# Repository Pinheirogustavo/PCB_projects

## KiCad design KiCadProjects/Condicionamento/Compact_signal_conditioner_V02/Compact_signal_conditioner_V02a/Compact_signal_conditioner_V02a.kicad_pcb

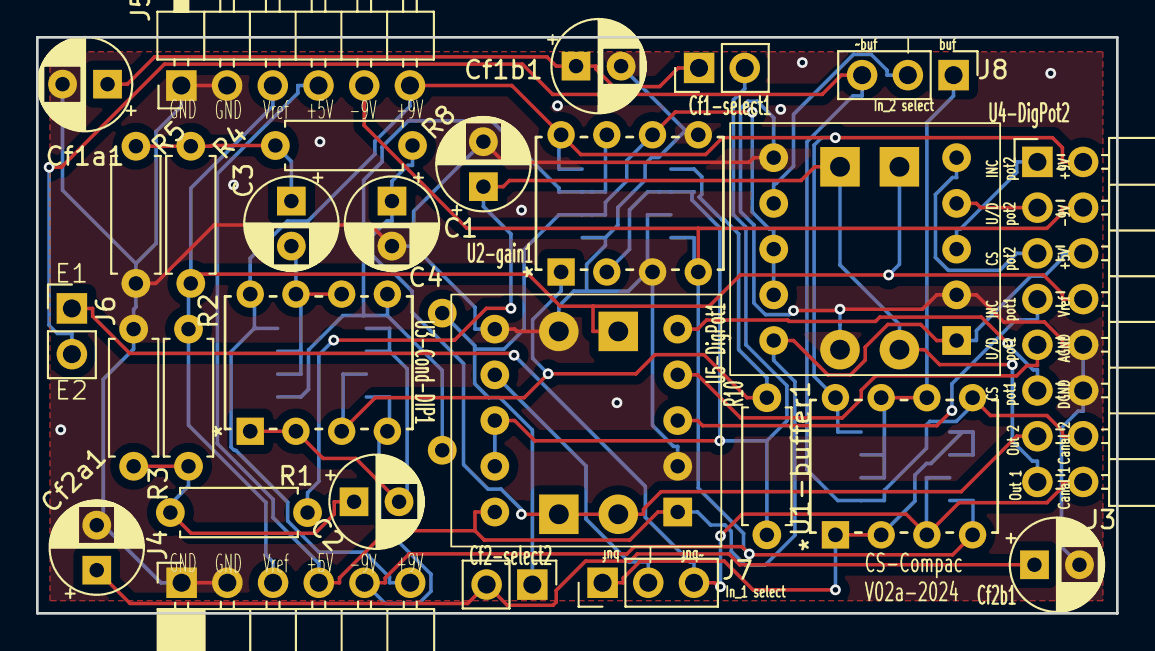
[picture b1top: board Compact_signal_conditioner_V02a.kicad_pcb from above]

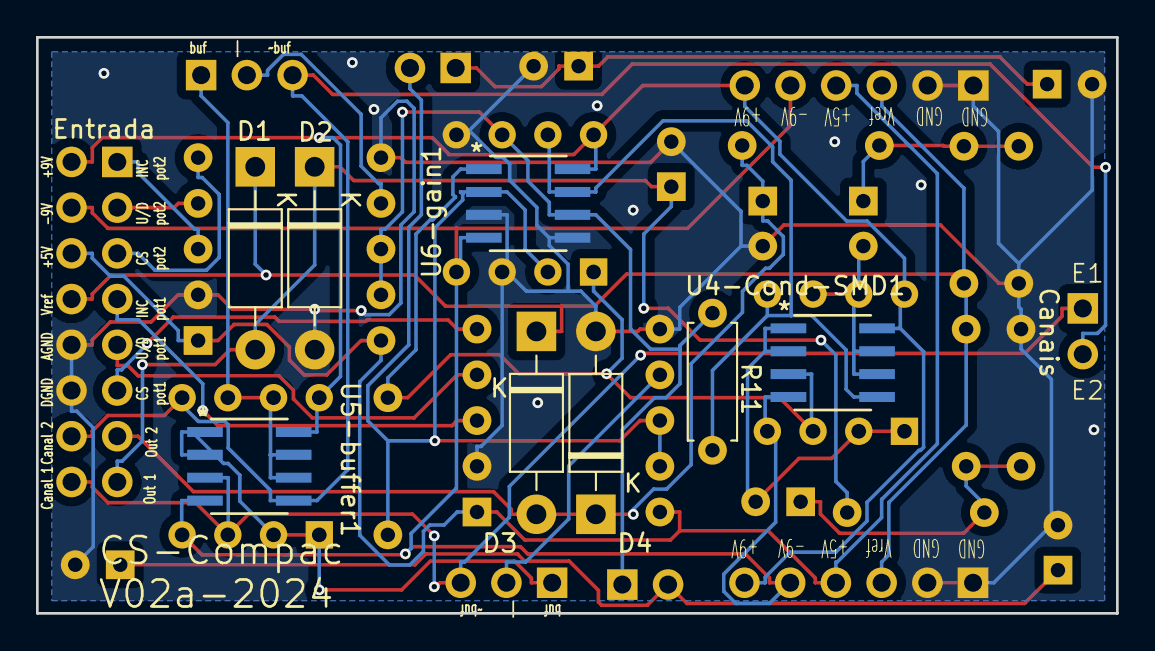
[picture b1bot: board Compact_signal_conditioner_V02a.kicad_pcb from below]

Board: 2 copper layers, 60.0 x 32.0 mm, 36 parts (8 on the bottom side), 29 nets.

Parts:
C1, C4: 470 pF; CP_Radial_D5.0mm_P2.50mm
C2, C3: 1 uF; CP_Radial_D5.0mm_P2.50mm
Cf1-select1: jumper cf1; PinHeader_1x02_P2.54mm_Vertical
Cf1a1, Cf1b1, Cf2a1, Cf2b1: C; CP_Radial_D5.0mm_P2.50mm
Cf2-select2: jumper cf2; PinHeader_1x02_P2.54mm_Vertical
D1, D2, D3, D4: 1N5819; D_DO-41_SOD81_P10.16mm_Horizontal
J3: Entrada; PinHeader_2x08_P2.54mm_Horizontal
J4: in; PinSocket_1x06_P2.54mm_Horizontal
J5: out; PinHeader_1x06_P2.54mm_Horizontal
J6: Canais; PinHeader_1x02_P2.54mm_Vertical
J7: In_1 select; PinHeader_1x03_P2.54mm_Vertical
J8: In_2 select; PinHeader_1x03_P2.54mm_Vertical
R1, R8: 220; R_Axial_DIN0207_L6.3mm_D2.5mm_P7.62mm_Horizontal
R2, R3, R4, R5: 100k; R_Axial_DIN0207_L6.3mm_D2.5mm_P7.62mm_Horizontal
R10, R11: 51k; R_Axial_DIN0207_L6.3mm_D2.5mm_P7.62mm_Horizontal
U1-buffer1, U2-gain1, U3-Cond-DIP1: AD828AN; N_8_ADI
U4-Cond-SMD1, U5-buffer1, U6-gain1: AD8056ARZ; R_8_ADI
U4-DigPot2, U5-DigPot1: X9c10x; X9c10X_module

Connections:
+5V: J3.3, J4.4, J5.4, U4-DigPot2.1 (VCC), U4-DigPot2.10 (VCC), U5-DigPot1.1 (VCC), U5-DigPot1.10 (VCC)
+9V: J3.1, J4.6, J5.6, U1-buffer1.8 (V+), U2-gain1.8 (V+), U3-Cond-DIP1.8 (V+), U4-Cond-SMD1.8 (VS+), U5-buffer1.8 (VS+), U6-gain1.8 (VS+)
-9V: J3.2, J4.5, J5.5, U1-buffer1.4 (V-), U2-gain1.4 (V-), U3-Cond-DIP1.4 (V-), U4-Cond-SMD1.4 (VS-), U5-buffer1.4 (VS-), U6-gain1.4 (VS-)
Canal_1: J3.8, J6.1, J7.3, U1-buffer1.3 (+IN1), U5-buffer1.3 (IN1+)
Canal_1_buffer: J7.1, U1-buffer1.1 (OUT1), U1-buffer1.2 (-IN1), U5-buffer1.1 (OUT1), U5-buffer1.2 (IN1-)
Canal_1_gain: R10.2, U2-gain1.1 (OUT1), U3-Cond-DIP1.3 (+IN1), U4-Cond-SMD1.3 (IN1+), U6-gain1.1 (OUT1)
Canal_2: J3.7, J6.2, J8.3, U1-buffer1.5 (+IN2), U5-buffer1.5 (IN2+)
Canal_2_buffer: J8.1, U1-buffer1.6 (-IN2), U1-buffer1.7 (OUT2), U5-buffer1.6 (IN2-), U5-buffer1.7 (OUT)
Canal_2_gain: R11.2, U2-gain1.7 (OUT2), U3-Cond-DIP1.5 (+IN2), U4-Cond-SMD1.5 (IN2+), U6-gain1.7 (OUT)
Earth: C1.2, C4.2, Cf1a1.2, Cf1b1.2, Cf2a1.2, Cf2b1.2, D2.2 (A), D4.2 (A), J3.5, J3.6, J4.1, J4.2, J5.1, J5.2, R3.2, R5.2, U2-gain1.3 (+IN1), U2-gain1.5 (+IN2), U4-DigPot2.2 (GND), U4-DigPot2.6 (GND), U5-DigPot1.2 (GND), U5-DigPot1.6 (GND), U6-gain1.3 (IN1+), U6-gain1.5 (IN2+)
In_gain_1: J7.2, U5-DigPot1.7 (RL)
In_gain_2: J8.2, U4-DigPot2.7 (RL)
unnamed: Cf1-select1.1, Cf1a1.1, Cf1b1.1
unnamed: Cf2-select2.2, Cf2a1.1, Cf2b1.1
Out_1: C1.1, D1.2 (A), D2.1 (K), J3.10, R1.2
Out_2: C4.1, D3.2 (A), D4.1 (K), J3.9, R8.2
Pot1_CS_(X9c104): J3.11, U5-DigPot1.5 (CS)
Pot1_X9c10x_INC: J3.13, U5-DigPot1.3 (INC)
Pot1_X9c10x_U/D: J3.12, U5-DigPot1.4 (U/D)
Pot2_CS_(X9c104): J3.14, U4-DigPot2.5 (CS)
Pot2_X9c10x_INC: J3.16, U4-DigPot2.3 (INC)
Pot2_X9c10x_U/D: J3.15, U4-DigPot2.4 (U/D)
Vref: D1.1 (K), D3.1 (K), J3.4, J4.3, J5.3, R2.1, R4.1
auxiliar_1: Cf1-select1.2, R10.1, U2-gain1.2 (-IN1), U5-DigPot1.8 (RW), U5-DigPot1.9 (RH), U6-gain1.2 (IN1-)
auxiliar_2: Cf2-select2.1, R11.1, U2-gain1.6 (-IN2), U4-DigPot2.8 (RW), U4-DigPot2.9 (RH), U6-gain1.6 (IN2-)
nó1: C2.2, U3-Cond-DIP1.1 (OUT1), U3-Cond-DIP1.2 (-IN1), U4-Cond-SMD1.1 (OUT1), U4-Cond-SMD1.2 (IN1-)
nó2: C2.1, R1.1, R2.2, R3.1
nó3: C3.2, U3-Cond-DIP1.6 (-IN2), U3-Cond-DIP1.7 (OUT2), U4-Cond-SMD1.6 (IN2-), U4-Cond-SMD1.7 (OUT)
nó4: C3.1, R4.2, R5.1, R8.1

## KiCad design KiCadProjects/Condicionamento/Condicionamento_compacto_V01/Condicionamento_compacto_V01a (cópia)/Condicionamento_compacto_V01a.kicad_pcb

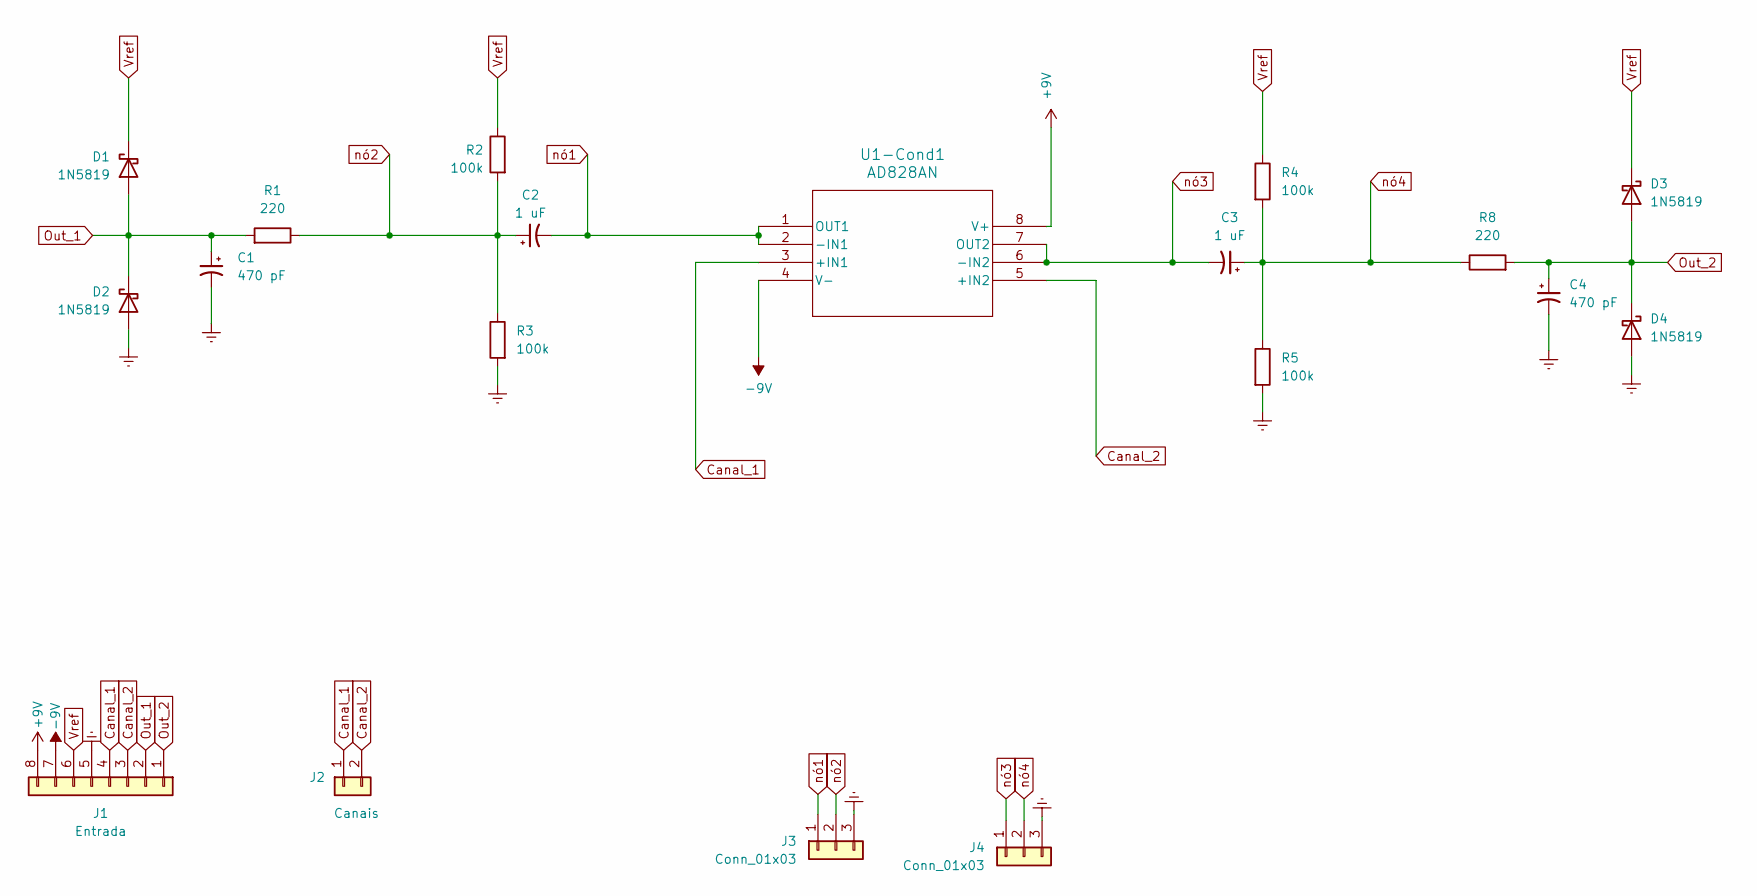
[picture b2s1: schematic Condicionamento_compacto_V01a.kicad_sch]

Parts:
C1, C4: 470 pF; CP_Radial_D5.0mm_P2.50mm
C2, C3: 1 uF; CP_Radial_D5.0mm_P2.50mm
D1, D2, D3, D4: 1N5819; D_DO-41_SOD81_P10.16mm_Horizontal
J1: Entrada; PinSocket_1x08_P2.54mm_Vertical
J2: Canais; PinHeader_1x02_P2.54mm_Vertical
J3, J4: Conn_01x03; PinHeader_1x03_P2.54mm_Vertical
R1, R8: 220; R_Axial_DIN0207_L6.3mm_D2.5mm_P7.62mm_Horizontal
R2, R3, R4, R5: 100k; R_Axial_DIN0207_L6.3mm_D2.5mm_P7.62mm_Horizontal
U1-Cond1: AD828AN; N_8_ADI

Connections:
+9V: J1.8, U1-Cond1.8 (V+)
-9V: J1.7, U1-Cond1.4 (V-)
Canal_1: J1.4, J2.1, U1-Cond1.3 (+IN1)
Canal_2: J1.3, J2.2, U1-Cond1.5 (+IN2)
Earth: C1.2, C4.2, D2.2 (A), D4.2 (A), J1.5, J3.3, J4.3, R3.2, R5.2
Out_1: C1.1, D1.2 (A), D2.1 (K), J1.2, R1.2
Out_2: C4.1, D3.2 (A), D4.1 (K), J1.1, R8.2
Vref: D1.1 (K), D3.1 (K), J1.6, R2.1, R4.1
nó1: C2.2, J3.1, U1-Cond1.1 (OUT1), U1-Cond1.2 (-IN1)
nó2: C2.1, J3.2, R1.1, R2.2, R3.1
nó3: C3.2, J4.1, U1-Cond1.6 (-IN2), U1-Cond1.7 (OUT2)
nó4: C3.1, J4.2, R4.2, R5.1, R8.1

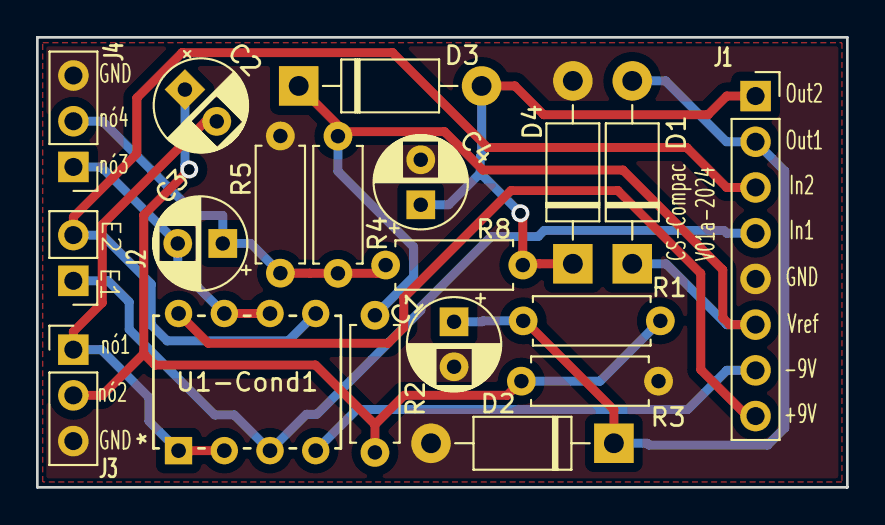
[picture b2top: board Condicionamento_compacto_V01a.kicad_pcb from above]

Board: 2 copper layers, 45.0 x 25.0 mm, 19 parts (0 on the bottom side), 12 nets.

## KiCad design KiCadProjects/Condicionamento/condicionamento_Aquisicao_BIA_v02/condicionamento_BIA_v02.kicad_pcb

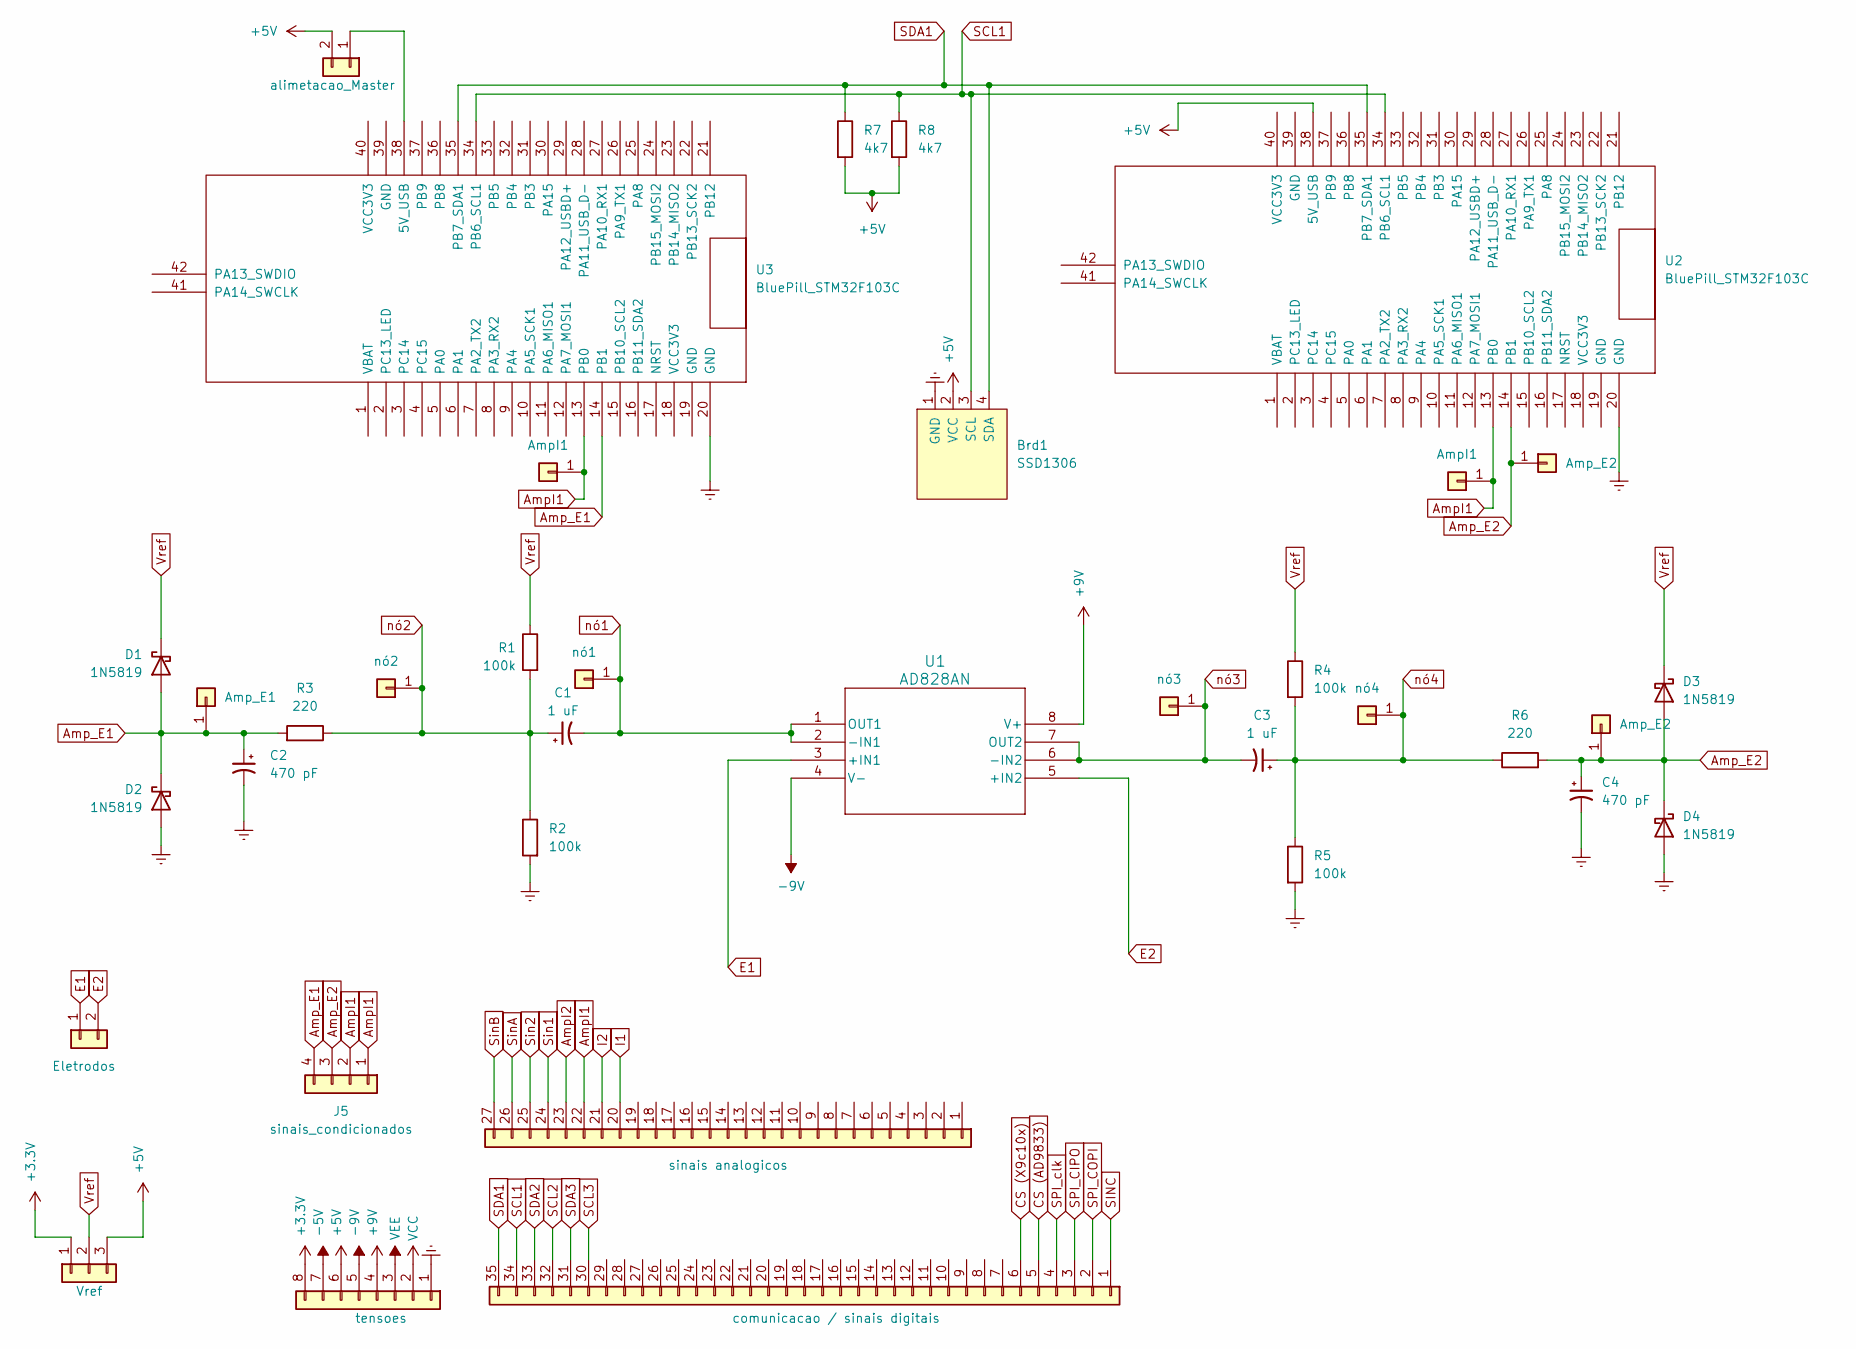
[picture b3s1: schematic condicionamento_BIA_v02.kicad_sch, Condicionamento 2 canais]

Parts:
Brd1: SSD1306; 128x64OLED
C1, C3: 1 uF; CP_Radial_D5.0mm_P2.50mm
C2, C4: 470 pF; CP_Radial_D5.0mm_P2.50mm
D1, D2, D3, D4: 1N5819; D_DO-41_SOD81_P10.16mm_Horizontal
J1: Vref; PinHeader_1x03_P2.54mm_Vertical
J2: tensoes; PinHeader_1x08_P2.54mm_Vertical
J3: sinais analogicos; PinHeader_1x27_P2.54mm_Vertical
J4: comunicacao / sinais digitais; PinHeader_1x35_P2.54mm_Vertical
J5: sinais_condicionados; PinHeader_1x04_P2.54mm_Horizontal
J6: alimetacao_Master; PinHeader_1x02_P2.54mm_Vertical
J7: Eletrodos; PinHeader_1x02_P2.54mm_Horizontal
J8: nó2; PinHeader_1x01_P2.54mm_Vertical
J9: nó1; PinHeader_1x01_P2.54mm_Vertical
J10: nó3; PinHeader_1x01_P2.54mm_Vertical
J11: nó4; PinHeader_1x01_P2.54mm_Vertical
J12: Amp_E1; PinHeader_1x01_P2.54mm_Vertical
J13, J16: Amp_E2; PinHeader_1x01_P2.54mm_Vertical
J15, J17: AmpI1; PinHeader_1x01_P2.54mm_Vertical
R1, R2, R4, R5: 100k; R_Axial_DIN0207_L6.3mm_D2.5mm_P7.62mm_Horizontal
R3, R6: 220; R_Axial_DIN0207_L6.3mm_D2.5mm_P7.62mm_Horizontal
R7, R8: 4k7; R_Axial_DIN0207_L6.3mm_D2.5mm_P7.62mm_Horizontal
U1: AD828AN; N_8_ADI
U2, U3: BluePill_STM32F103C

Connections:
+3.3V: J1.1, J2.8; also elsewhere on the board
+5V: Brd1.2 (VCC), J1.3, J2.6, J6.2, R7.2, R8.2, U2.38 (5V_USB); also elsewhere on the board
+9V: J2.4, U1.8 (V+)
-5V: J2.7
-9V: J2.5, U1.4 (V-)
AmpI1: J3.22, J5.1, J5.2, J15.1, J17.1, U2.13 (PB0), U3.13 (PB0)
AmpI2: J3.23
Amp_E1: C2.1, D1.2 (A), D2.1 (K), J5.4, J12.1, R3.2, U3.14 (PB1)
Amp_E2: C4.1, D3.2 (A), D4.1 (K), J5.3, J13.1, J16.1, R6.2, U2.14 (PB1)
CS (AD9833): J4.5
CS (X9c10x): J4.6
E1: J7.1, U1.3 (+IN1)
E2: J7.2, U1.5 (+IN2)
Earth: Brd1.1 (GND), C2.2, C4.2, D2.2 (A), D4.2 (A), J2.1, R2.2, R5.2, U2.20 (GND), U3.20 (GND); also elsewhere on the board
I1: J3.20
I2: J3.21
unnamed: J6.1, U3.38 (5V_USB)
SCL1: Brd1.3 (SCL), J4.34, R8.1, U2.34 (PB6_SCL1), U3.34 (PB6_SCL1); also elsewhere on the board
SCL2: J4.32
SCL3: J4.30
SDA1: Brd1.4 (SDA), J4.35, R7.1, U2.35 (PB7_SDA1), U3.35 (PB7_SDA1); also elsewhere on the board
SDA2: J4.33
SDA3: J4.31
SINC: J4.1
SPI_CIPO: J4.3
SPI_COPI: J4.2
SPI_clk: J4.4
Sin1: J3.24
Sin2: J3.25
SinA: J3.26
SinB: J3.27
VCC: J2.2
VEE: J2.3
Vref: D1.1 (K), D3.1 (K), J1.2, R1.1, R4.1; also elsewhere on the board
nó1: C1.2, J9.1, U1.1 (OUT1), U1.2 (-IN1)
nó2: C1.1, J8.1, R1.2, R2.1, R3.1
nó3: C3.2, J10.1, U1.6 (-IN2), U1.7 (OUT2)
nó4: C3.1, J11.1, R4.2, R5.1, R6.1

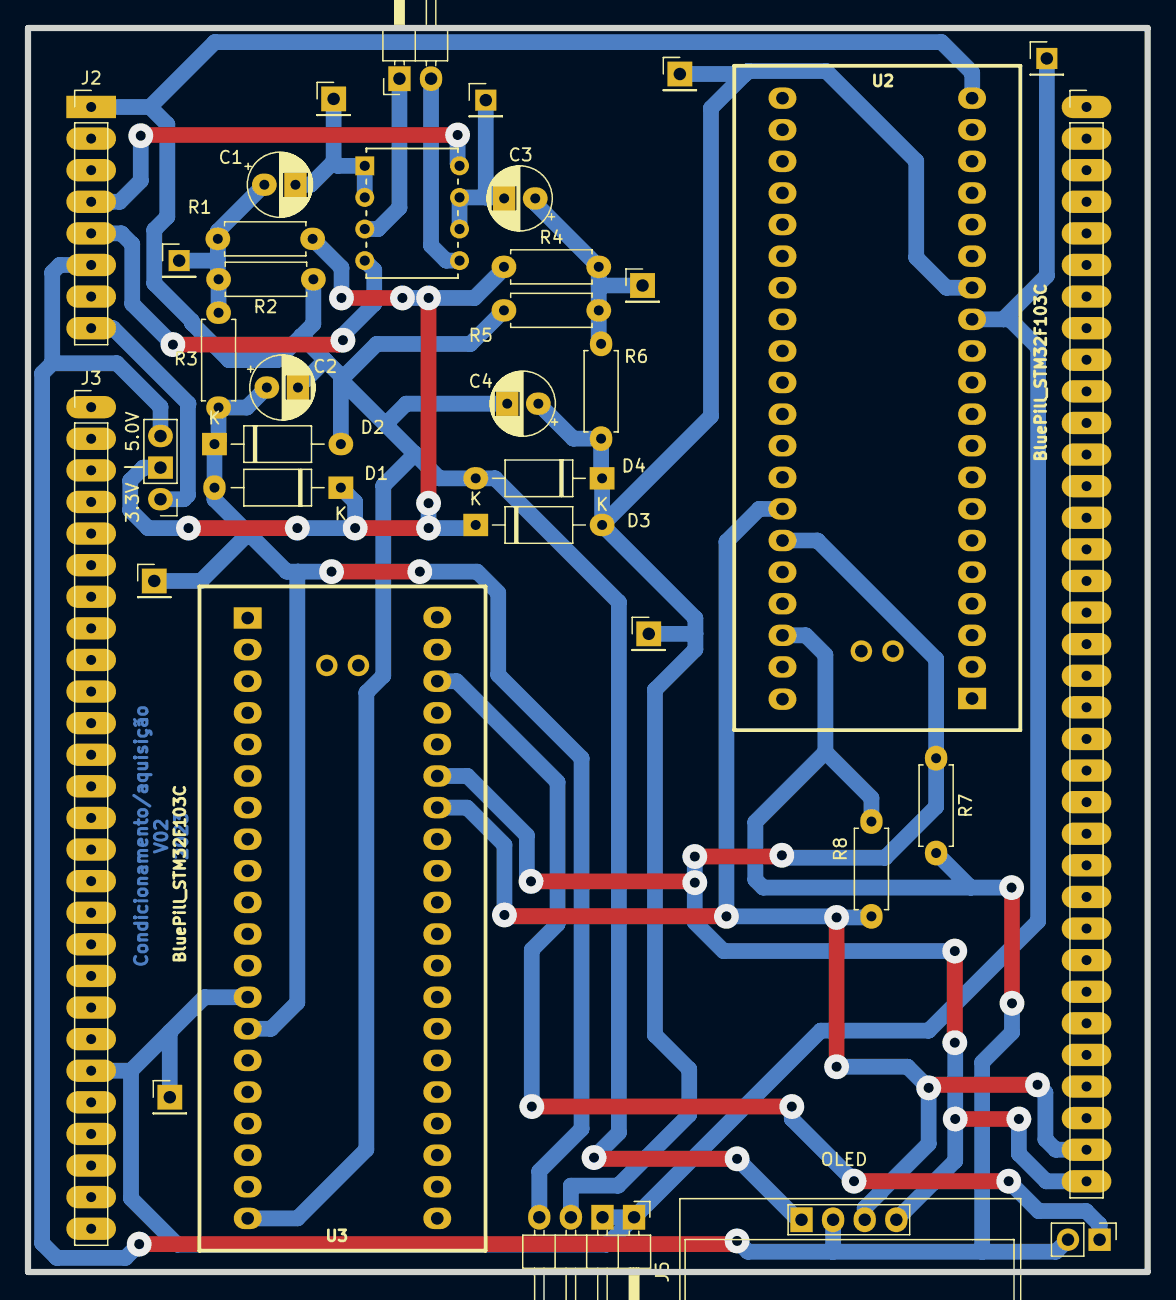
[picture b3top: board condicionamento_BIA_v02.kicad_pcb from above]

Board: 2 copper layers, 90.0 x 100.0 mm, 36 parts (0 on the bottom side), 18 nets.

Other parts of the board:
3.3V | 5.0V: Vref; PinHeader_1x03_P2.54mm_Vertical
OLED: SSD1306; 128x64OLED

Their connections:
+3.3V: 3.3V | 5.0V.1; also elsewhere on the board
+5V: 3.3V | 5.0V.3, OLED.2 (VCC); also elsewhere on the board
Earth: OLED.1 (GND); also elsewhere on the board
SCL1: OLED.3 (SCL); also elsewhere on the board
SDA1: OLED.4 (SDA); also elsewhere on the board
Vref: 3.3V | 5.0V.2; also elsewhere on the board

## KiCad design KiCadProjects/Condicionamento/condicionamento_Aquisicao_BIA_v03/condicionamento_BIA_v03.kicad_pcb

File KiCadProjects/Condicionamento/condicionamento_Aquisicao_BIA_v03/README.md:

# Circuito de condicionamento e aquisição de sinal

## Descrição Geral do projeto

Sistema projetado para permitir a aquisição de sinais por meio dos dois ADCs presentes em cada microcontrolador STM32.

Estágios: Sinais a serem condicionados &rarr; buffer &rarr; offset (valor médio do limite de entrada do ADC) &rarr; diodos de proteção ( limites de entrada do ADC) &rarr; Filtro anti-aliasing &rarr; sinal condicionado &rarr; ADC@STM32

## Sinais do circuito:

- AmplI1: Tensão de saída **já condicionada** do INA que monitora a corrente I1
- Amp_E1: Tensão medida pelo eletrodo proximal do pé/mão
- Amp_E2: Tensão medida pelo eletrodo proximal do pé/mão

##Cuidados a serem tomados

O conjunto de pinos **Vref** permite selecionar sinais e 3.3V e 5.0V. A escolha do sinal deve ser adequada ao limite de entrada dos pinos ADCs do microcontrolador utilizado. Para o STM32 esse limite é de 3.3V.

Todos os sinais que são enviados aos pinos de ADCs dos microcontroladores devem estar devidamente condicionados.

Sobre a alimentação dos microcontroladores: O par de pinos "alimentacao_Master" fornece uma alimentação de +5V  ao Master quando é fechado. Esse  par de pinos deve permanecer aberto quando o microcontrolador Master estiver conectado ao computador por meio de cabo USB, pois o pino de 5V do STM32 é diretamente conectada à alimentação fornecida por USB, sem qualquer circuito de proteção. O microcontrolador Slave está sempre conectado à alimentação de 5V do sistema. Somente conecte esse dispositivo ao computador se o sistema estiver desligado. 

## Estágios do circuito

#### Circuito de condicionamento

O circuito de condicionamento permite a adequada aquisição de sinal por meio de microcontrolador, garantindo que os sinais aplicados nas entradas do dispositivo não ultrapassem os limites de tensão e corrente suportados, além da adequada amostragem do sinal, por meio de filtro anti-aliasing. Esse circuito emprega o amplificador operacional dual AD826/828, o que permite o condicionamento de dois canais. Os estágios do circuito são: 

- buffer: amplificador operacional no modo seguidor, configuração de alta impedância de entrada que permite o adequado acoplamento entre os estágios do sistema, minimizando a interação entre eles.

- Offset: estágio que realiza um deslocamento (offset) do sinal de entrada, adequando os sinais alternados de correntes do circuito aos ADCs do microcontrolador, adicionando um sinal DC equivalente ao valor médio do limite de entrada dos ADCS. O valor de Vref deve ser definido pelo operador de acordo com esse limite.

- Diodos de proteção: não permitem que o sinal de entrada ultrapasse  os limites de entrada do conversor ADC. O valor de Vref deve ser definido pelo operador de acordo com esse limite.

- filtro anti-alising: Frequência de corte $F_c$:

$$F_c = \frac{1}{2\cdot\pi\cdot R\cdot C} = \frac{1}{2\cdot\pi\cdot220\cdot470\cdot10 ^{-12}} = 1,5 MHz$$

#### Microcontroladores

Dois microcontroladores são empregados nesse sistema de BIA, permitindo a leitura de 4 canais de medição. A comunicação entre eles é feita por meio do protocolo I2C. Ambos leem o sinal de amplitude da corrente medida pelo INA (AmpI1) em seus ADCs.

- STM32 Master

O par de pinos "alimentacao_Master" fornece uma alimentação de +5V quando é fechado. Esse  par de pinos deve permanecer aberto quando o microcontrolador estiver conectado ao computador por meio de cabo USB, pois o pino de 5V do STM32 é diretamente conectada à alimentação fornecida por USB, sem qualquer circuito de proteção.

> ADC1: Pino B0 recebe o sinal de amplitude de corrente AmpI1

> ADC2: Pino B1 recebe o sinal de amplitude de tensão do eletrodo de medição E1.

- STM32 Slave

O microcontrolador está sempre conectado à alimentação de 5V do sistema. Somente conecte esse dispositivo ao computador se o sistema estiver desligado. 

> ADC1: Pino B0 recebe o sinal de amplitude de corrente AmpI1

> ADC2: Pino B1 recebe o sinal de amplitude de tensão do eletrodo de medição E2.

## Esquemático

## PCB

## PCB-3D

## PCB Máscara

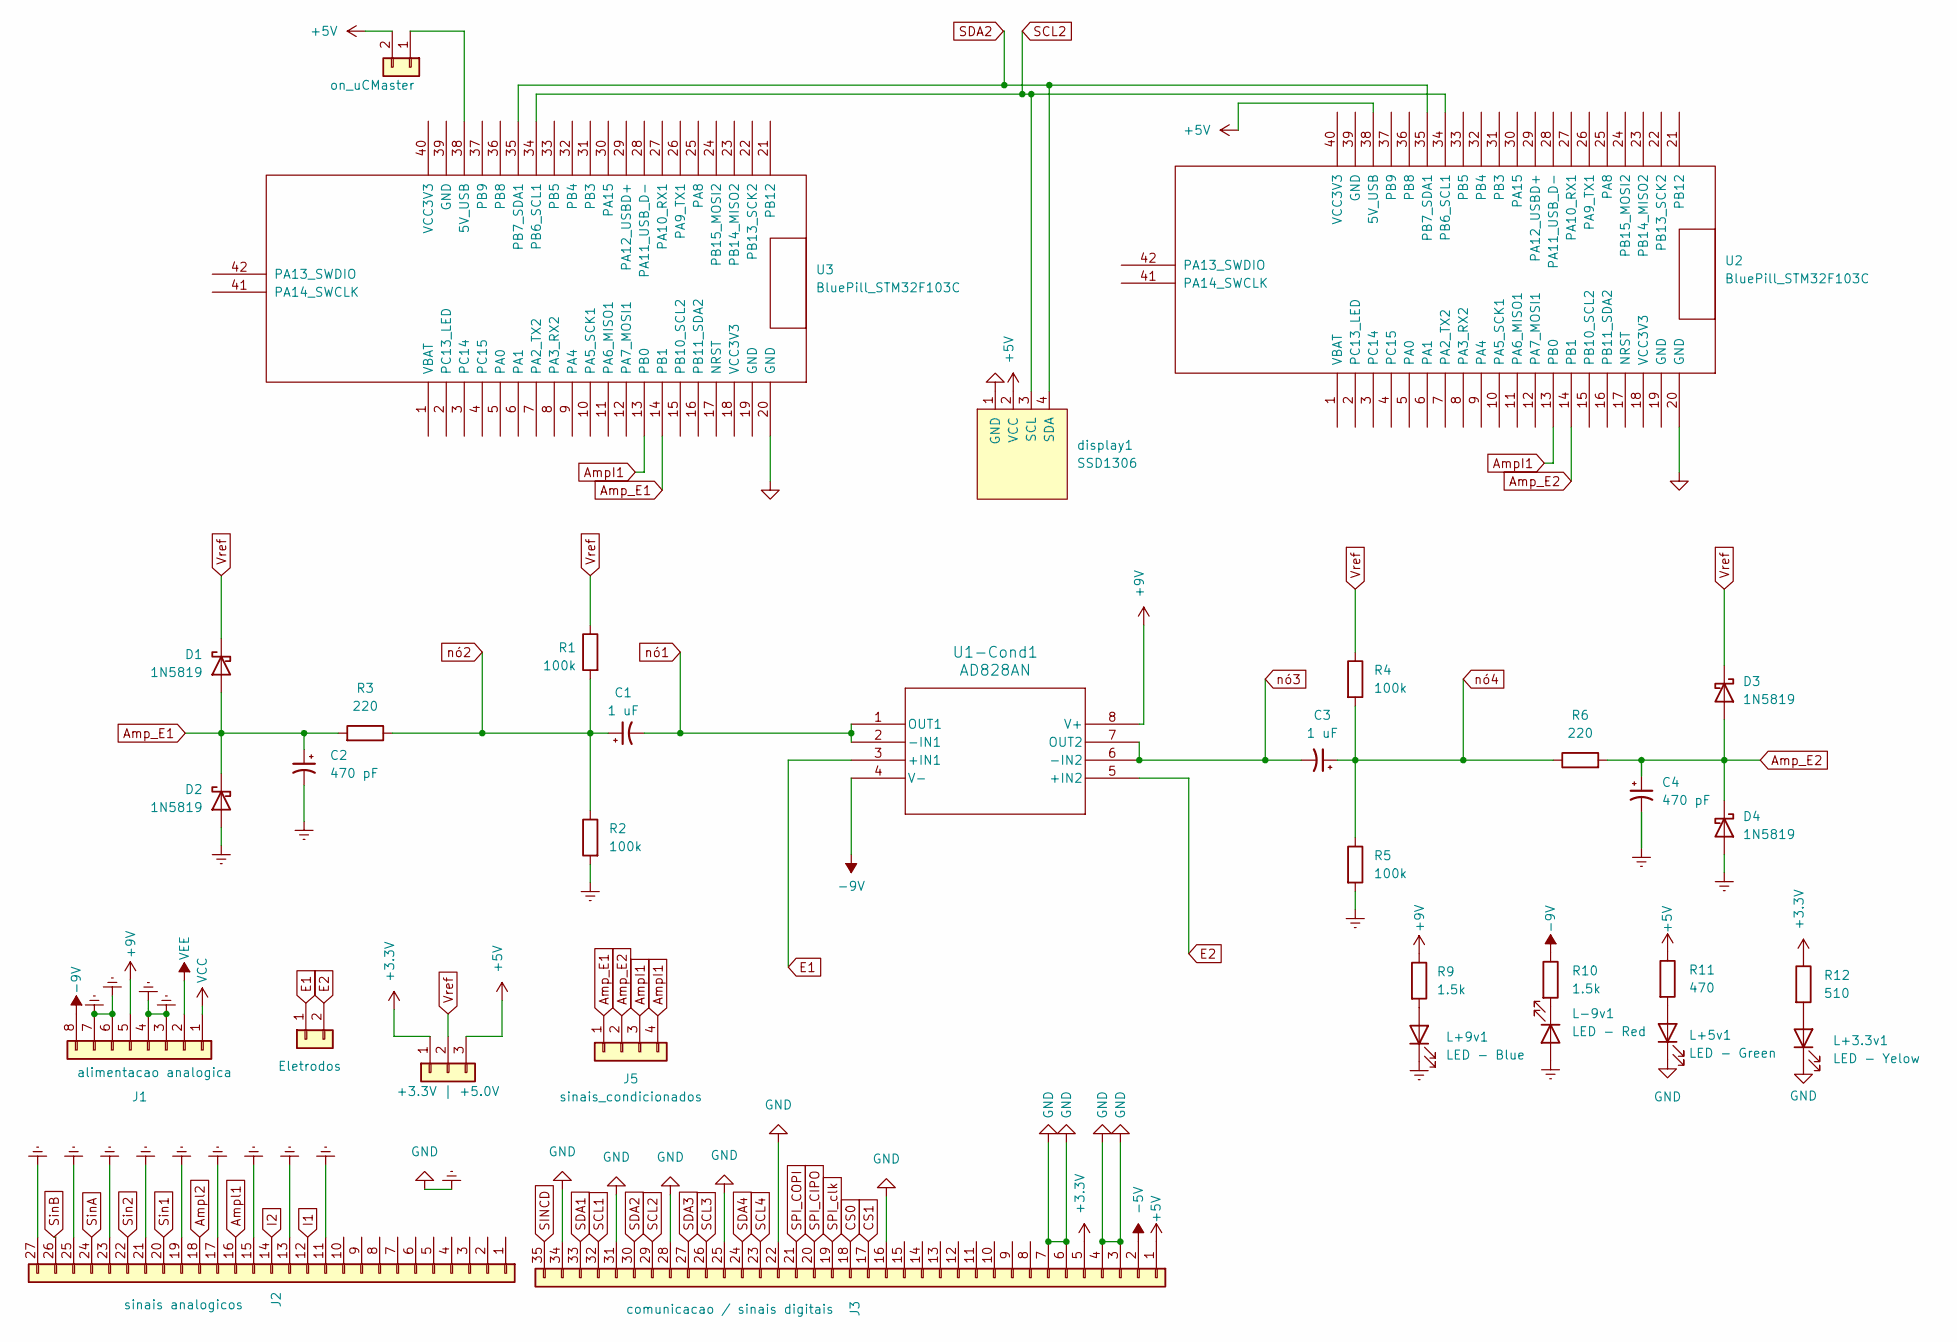
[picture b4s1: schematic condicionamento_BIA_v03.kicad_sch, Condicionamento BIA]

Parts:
C1, C3: 1 uF; CP_Radial_D5.0mm_P2.50mm
C2, C4: 470 pF; CP_Radial_D5.0mm_P2.50mm
D1, D2, D3, D4: 1N5819; D_DO-41_SOD81_P10.16mm_Horizontal
J1: alimentacao analogica; PinHeader_1x08_P2.54mm_Vertical
J2: sinais analogicos; PinHeader_1x27_P2.54mm_Vertical
J3: comunicacao / sinais digitais; PinHeader_1x35_P2.54mm_Vertical
J4: +3.3V | +5.0V; PinHeader_1x03_P2.54mm_Vertical
J5: sinais_condicionados; PinHeader_1x04_P2.54mm_Horizontal
J6: Eletrodos; PinHeader_1x02_P2.54mm_Horizontal
J7: on_uCMaster; PinHeader_1x02_P2.54mm_Vertical
L+3.3v1: LED - Yelow; LED_D5.0mm
L+5v1: LED - Green; LED_D5.0mm
L+9v1: LED - Blue; LED_D5.0mm
L-9v1: LED - Red; LED_D5.0mm
R1, R2, R4, R5: 100k; R_Axial_DIN0207_L6.3mm_D2.5mm_P7.62mm_Horizontal
R3, R6: 220; R_Axial_DIN0207_L6.3mm_D2.5mm_P7.62mm_Horizontal
R9, R10: 1.5k; R_Axial_DIN0207_L6.3mm_D2.5mm_P7.62mm_Horizontal
R11: 470; R_Axial_DIN0207_L6.3mm_D2.5mm_P7.62mm_Horizontal
R12: 510; R_Axial_DIN0207_L6.3mm_D2.5mm_P7.62mm_Horizontal
U1-Cond1: AD828AN; AD828
U2, U3: BluePill_STM32F103C
display1: SSD1306; 128x64OLED

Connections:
+3.3V: J3.5, J4.1, R12.1
+5V: J3.1, J4.3, J7.2, R11.1, U2.38 (5V_USB), display1.2 (VCC)
+9V: J1.5, R9.1, U1-Cond1.8 (V+)
-5V: J3.2
-9V: J1.8, R10.1, U1-Cond1.4 (V-)
AmpI1: J5.3, J5.4, U2.13 (PB0), U3.13 (PB0)
Amp_E1: C2.1, D1.2 (A), D2.1 (K), J5.1, R3.2, U3.14 (PB1)
Amp_E2: C4.1, D3.2 (A), D4.1 (K), J5.2, R6.2, U2.14 (PB1)
Ampl1: J2.16
Ampl2: J2.18
CS0: J3.18
CS1: J3.17
E1: J6.1, U1-Cond1.3 (+IN1)
E2: J6.2, U1-Cond1.5 (+IN2)
Earth: C2.2, C4.2, D2.2 (A), D4.2 (A), J1.3, J1.4, J1.6, J1.7, J2.11, J2.13, J2.15, J2.17, J2.19, J2.21, J2.23, J2.25, J2.27, J3.3, J3.4, J3.6, J3.7, J3.16, J3.22, J3.25, J3.28, J3.31, J3.34, L+3.3v1.1 (K), L+5v1.1 (K), L+9v1.1 (K), L-9v1.2 (A), R2.2, R5.2, U2.20 (GND), U3.20 (GND), display1.1 (GND)
I1: J2.12
I2: J2.14
unnamed: J7.1, U3.38 (5V_USB)
unnamed: L+3.3v1.2 (A), R12.2
unnamed: L+5v1.2 (A), R11.2
unnamed: L+9v1.2 (A), R9.2
unnamed: L-9v1.1 (K), R10.2
SCL1: J3.32
SCL2: J3.29, U2.34 (PB6_SCL1), U3.34 (PB6_SCL1), display1.3 (SCL)
SCL3: J3.26
SCL4: J3.23
SDA1: J3.33
SDA2: J3.30, U2.35 (PB7_SDA1), U3.35 (PB7_SDA1), display1.4 (SDA)
SDA3: J3.27
SDA4: J3.24
SINCD: J3.35
SPI_CIPO: J3.20
SPI_COPI: J3.21
SPI_clk: J3.19
Sin1: J2.20
Sin2: J2.22
SinA: J2.24
SinB: J2.26
VCC: J1.1
VEE: J1.2
Vref: D1.1 (K), D3.1 (K), J4.2, R1.1, R4.1
nó1: C1.2, U1-Cond1.1 (OUT1), U1-Cond1.2 (-IN1)
nó2: C1.1, R1.2, R2.1, R3.1
nó3: C3.2, U1-Cond1.6 (-IN2), U1-Cond1.7 (OUT2)
nó4: C3.1, R4.2, R5.1, R6.1

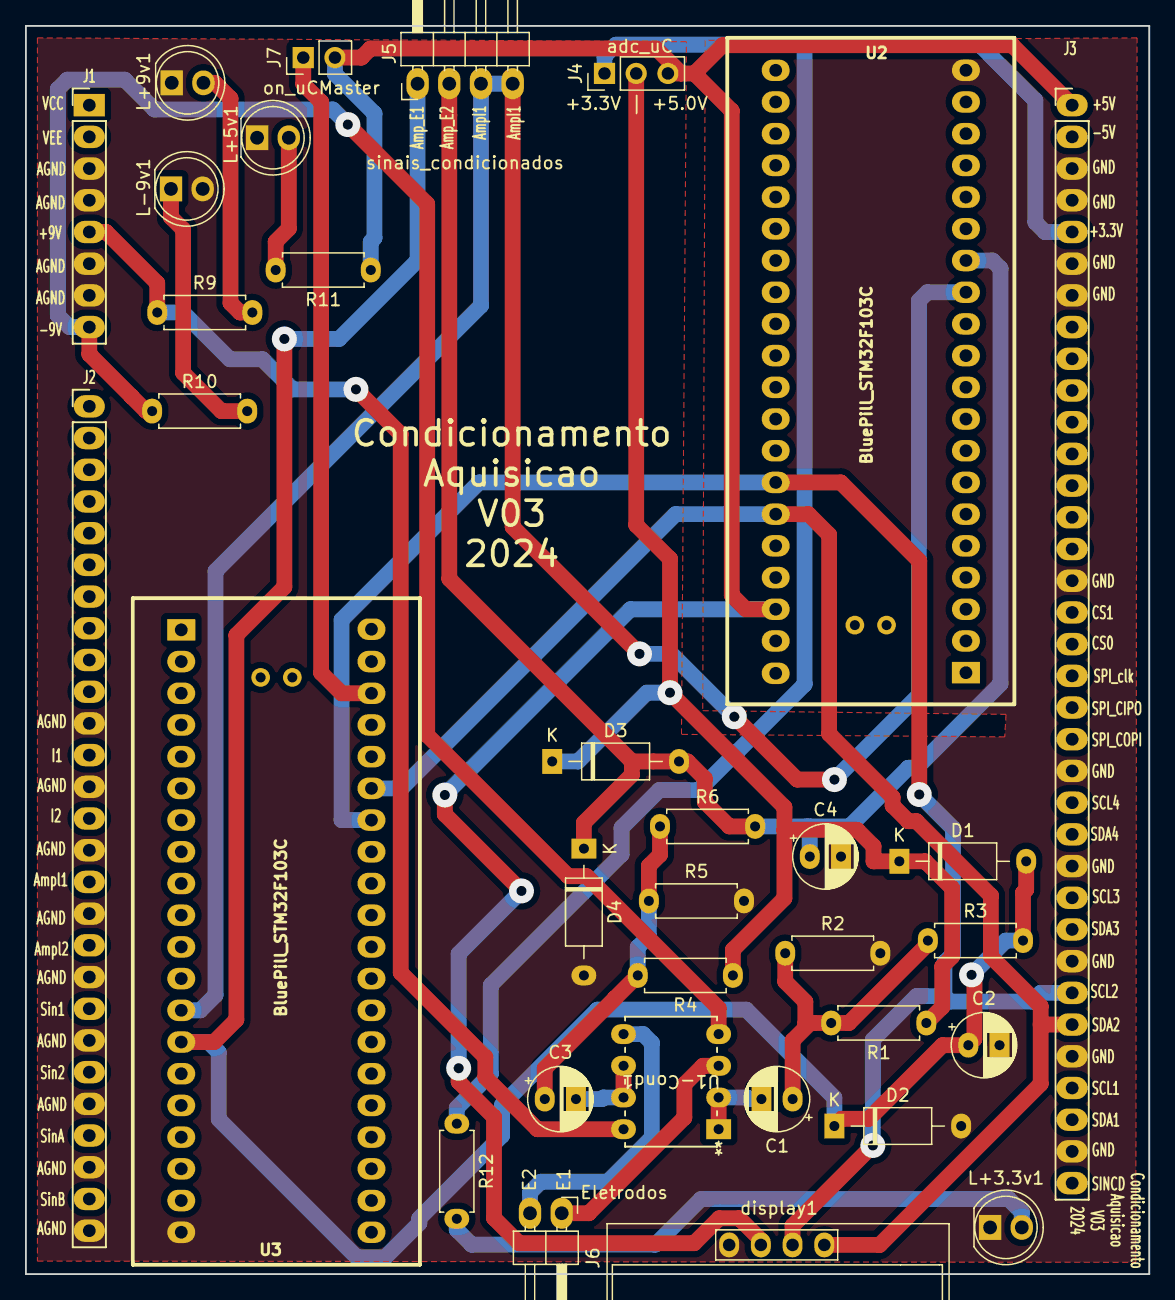
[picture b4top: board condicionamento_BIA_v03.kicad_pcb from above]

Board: 2 copper layers, 90.0 x 100.0 mm, 33 parts (0 on the bottom side), 22 nets.

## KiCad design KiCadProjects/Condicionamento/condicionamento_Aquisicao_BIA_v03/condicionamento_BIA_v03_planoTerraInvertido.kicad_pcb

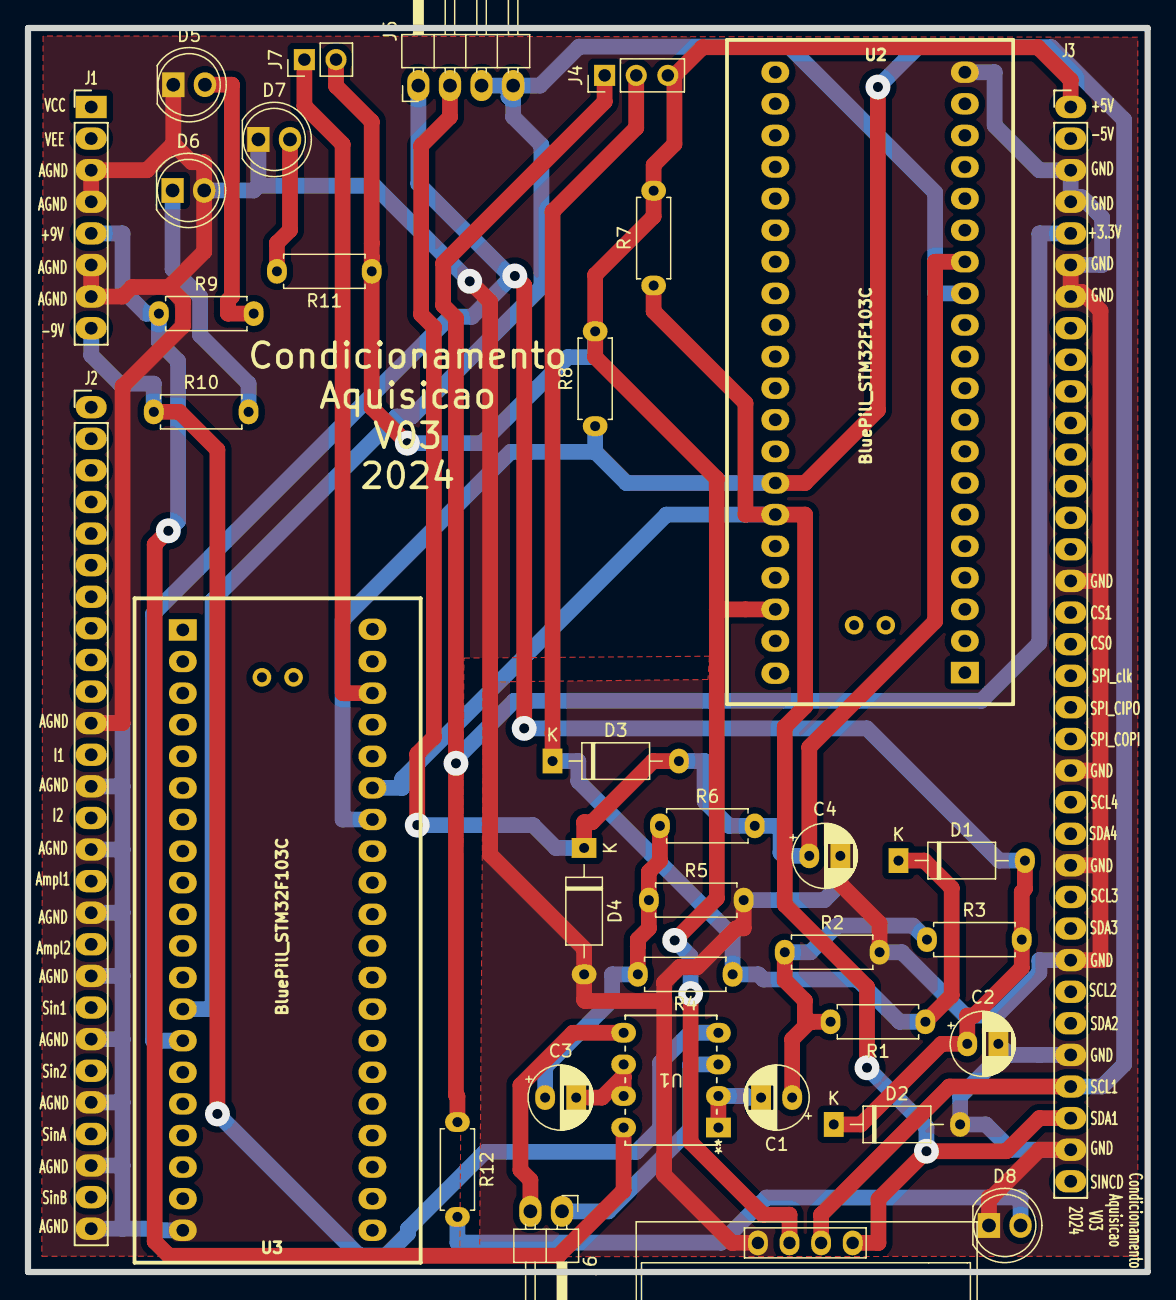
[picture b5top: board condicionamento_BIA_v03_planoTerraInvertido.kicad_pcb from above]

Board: 2 copper layers, 90.0 x 100.0 mm, 35 parts (0 on the bottom side), 22 nets.

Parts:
Brd1: SSD1306; 128x64OLED
C1, C3: 1 uF; CP_Radial_D5.0mm_P2.50mm
C2, C4: 470 pF; CP_Radial_D5.0mm_P2.50mm
D1, D2, D3, D4: 1N5819; D_DO-41_SOD81_P10.16mm_Horizontal
D5: LED - Blue; LED_D5.0mm
D6: LED - Red; LED_D5.0mm
D7: LED - Green; LED_D5.0mm
D8: LED - Yelow; LED_D5.0mm
J1: alimentacao analogica; PinHeader_1x08_P2.54mm_Vertical
J2: sinais analogicos; PinHeader_1x27_P2.54mm_Vertical
J3: comunicacao / sinais digitais; PinHeader_1x35_P2.54mm_Vertical
J4: Vref; PinHeader_1x03_P2.54mm_Vertical
J5: sinais_condicionados; PinHeader_1x04_P2.54mm_Horizontal
J6: Eletrodos; PinHeader_1x02_P2.54mm_Horizontal
J7: alimetacao_Master; PinHeader_1x02_P2.54mm_Vertical
R1, R2, R4, R5: 100k; R_Axial_DIN0207_L6.3mm_D2.5mm_P7.62mm_Horizontal
R3, R6: 220; R_Axial_DIN0207_L6.3mm_D2.5mm_P7.62mm_Horizontal
R7, R8: 4k7; R_Axial_DIN0207_L6.3mm_D2.5mm_P7.62mm_Horizontal
R9: 390; R_Axial_DIN0207_L6.3mm_D2.5mm_P7.62mm_Horizontal
R10: 360; R_Axial_DIN0207_L6.3mm_D2.5mm_P7.62mm_Horizontal
R11: 160; R_Axial_DIN0207_L6.3mm_D2.5mm_P7.62mm_Horizontal
R12: 82; R_Axial_DIN0207_L6.3mm_D2.5mm_P7.62mm_Horizontal
U1: AD828AN; AD828
U2, U3: BluePill_STM32F103C

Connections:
+3.3V: J3.5, J4.1, R12.1
+5V: Brd1.2 (VCC), J3.1, J4.3, J7.2, R7.2, R8.2, R11.1, U2.38 (5V_USB)
+9V: J1.5, R9.1, U1.8 (V+)
-9V: J1.8, R10.1, U1.4 (V-)
AmpI1: J5.3, J5.4, U2.13 (PB0), U3.13 (PB0)
Amp_E1: C2.1, D1.2 (A), D2.1 (K), J5.1, R3.2, U3.14 (PB1)
Amp_E2: C4.1, D3.2 (A), D4.1 (K), J5.2, R6.2, U2.14 (PB1)
E1: J6.1, U1.3 (+IN1)
E2: J6.2, U1.5 (+IN2)
Earth: Brd1.1 (GND), C2.2, C4.2, D2.2 (A), D4.2 (A), D5.1 (K), D6.2 (A), D7.1 (K), D8.1 (K), J1.3, J1.4, J1.6, J1.7, J2.11, J2.13, J2.15, J2.17, J2.19, J2.21, J2.23, J2.25, J2.27, J3.3, J3.4, J3.6, J3.7, J3.16, J3.22, J3.25, J3.28, J3.31, J3.34, R2.2, R5.2, U2.20 (GND), U3.20 (GND)
unnamed: D5.2 (A), R9.2
unnamed: D6.1 (K), R10.2
unnamed: D7.2 (A), R11.2
unnamed: D8.2 (A), R12.2
unnamed: J7.1, U3.38 (5V_USB)
SCL1: Brd1.3 (SCL), J3.32, R8.1, U2.34 (PB6_SCL1), U3.34 (PB6_SCL1)
SDA1: Brd1.4 (SDA), J3.33, R7.1, U2.35 (PB7_SDA1), U3.35 (PB7_SDA1)
Vref: D1.1 (K), D3.1 (K), J4.2, R1.1, R4.1
nó1: C1.2, U1.1 (OUT1), U1.2 (-IN1)
nó2: C1.1, R1.2, R2.1, R3.1
nó3: C3.2, U1.6 (-IN2), U1.7 (OUT2)
nó4: C3.1, R4.2, R5.1, R6.1
